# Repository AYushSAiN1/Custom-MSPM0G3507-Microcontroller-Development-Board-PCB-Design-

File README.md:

# MSPM0G3507 Microcontroller Development Board

## Overview
This project presents the design of a custom development board based on the Texas Instruments MSPM0G3507 microcontroller. The objective of this project is to explore the workflow of embedded hardware development including schematic design, PCB layout, power regulation, debugging interfaces, and communication peripherals.

The board integrates essential subsystems required for microcontroller operation such as power management, USB-UART communication, clock generation, and SWD debugging support.

---

## Key Features

- MSPM0G3507 ARM Cortex-M0+ microcontroller
- USB-C interface for power input
- 3.3V LDO voltage regulator
- USB-UART communication using CH340
- SWD debugging interface
- External crystal oscillator
- Decoupling and filtering circuitry for stable operation

---

## Hardware Architecture

### USB Interface
- USB-C connector for power input
- VBUS supply input

### Power Regulation
- 3.3V LDO voltage regulator
- Input and output filtering capacitors

### USB-UART Communication
- CH340 USB-to-UART converter
- Serial communication with MCU

### Microcontroller Core
- MSPM0G3507 MCU
- Decoupling capacitors
- GPIO expansion

### Clock Circuit
- External crystal oscillator
- Load capacitors

### Debug Interface
- ARM SWD debug header
- Reset circuitry
## Schematic Preview

---

## PCB Layout

---

## PCB 3D View

---
---
## Learning Outcomes

- Microcontroller hardware integration
- Power supply design for embedded systems
- USB-UART communication interface
- PCB schematic capture and layout
- Decoupling and grounding strategies
- SWD debugging interface design

---

## Future Improvements

- Add sensor interfaces (I2C / SPI peripherals)
- Improve PCB routing for signal integrity
- Add onboard debugging LEDs
- Integrate bootloader support

---
## Tools Used

- KiCad — schematic capture and PCB layout
- Embedded hardware design principles
- PCB routing and layout techniques

---

## License

This project is released for educational and learning purposes.

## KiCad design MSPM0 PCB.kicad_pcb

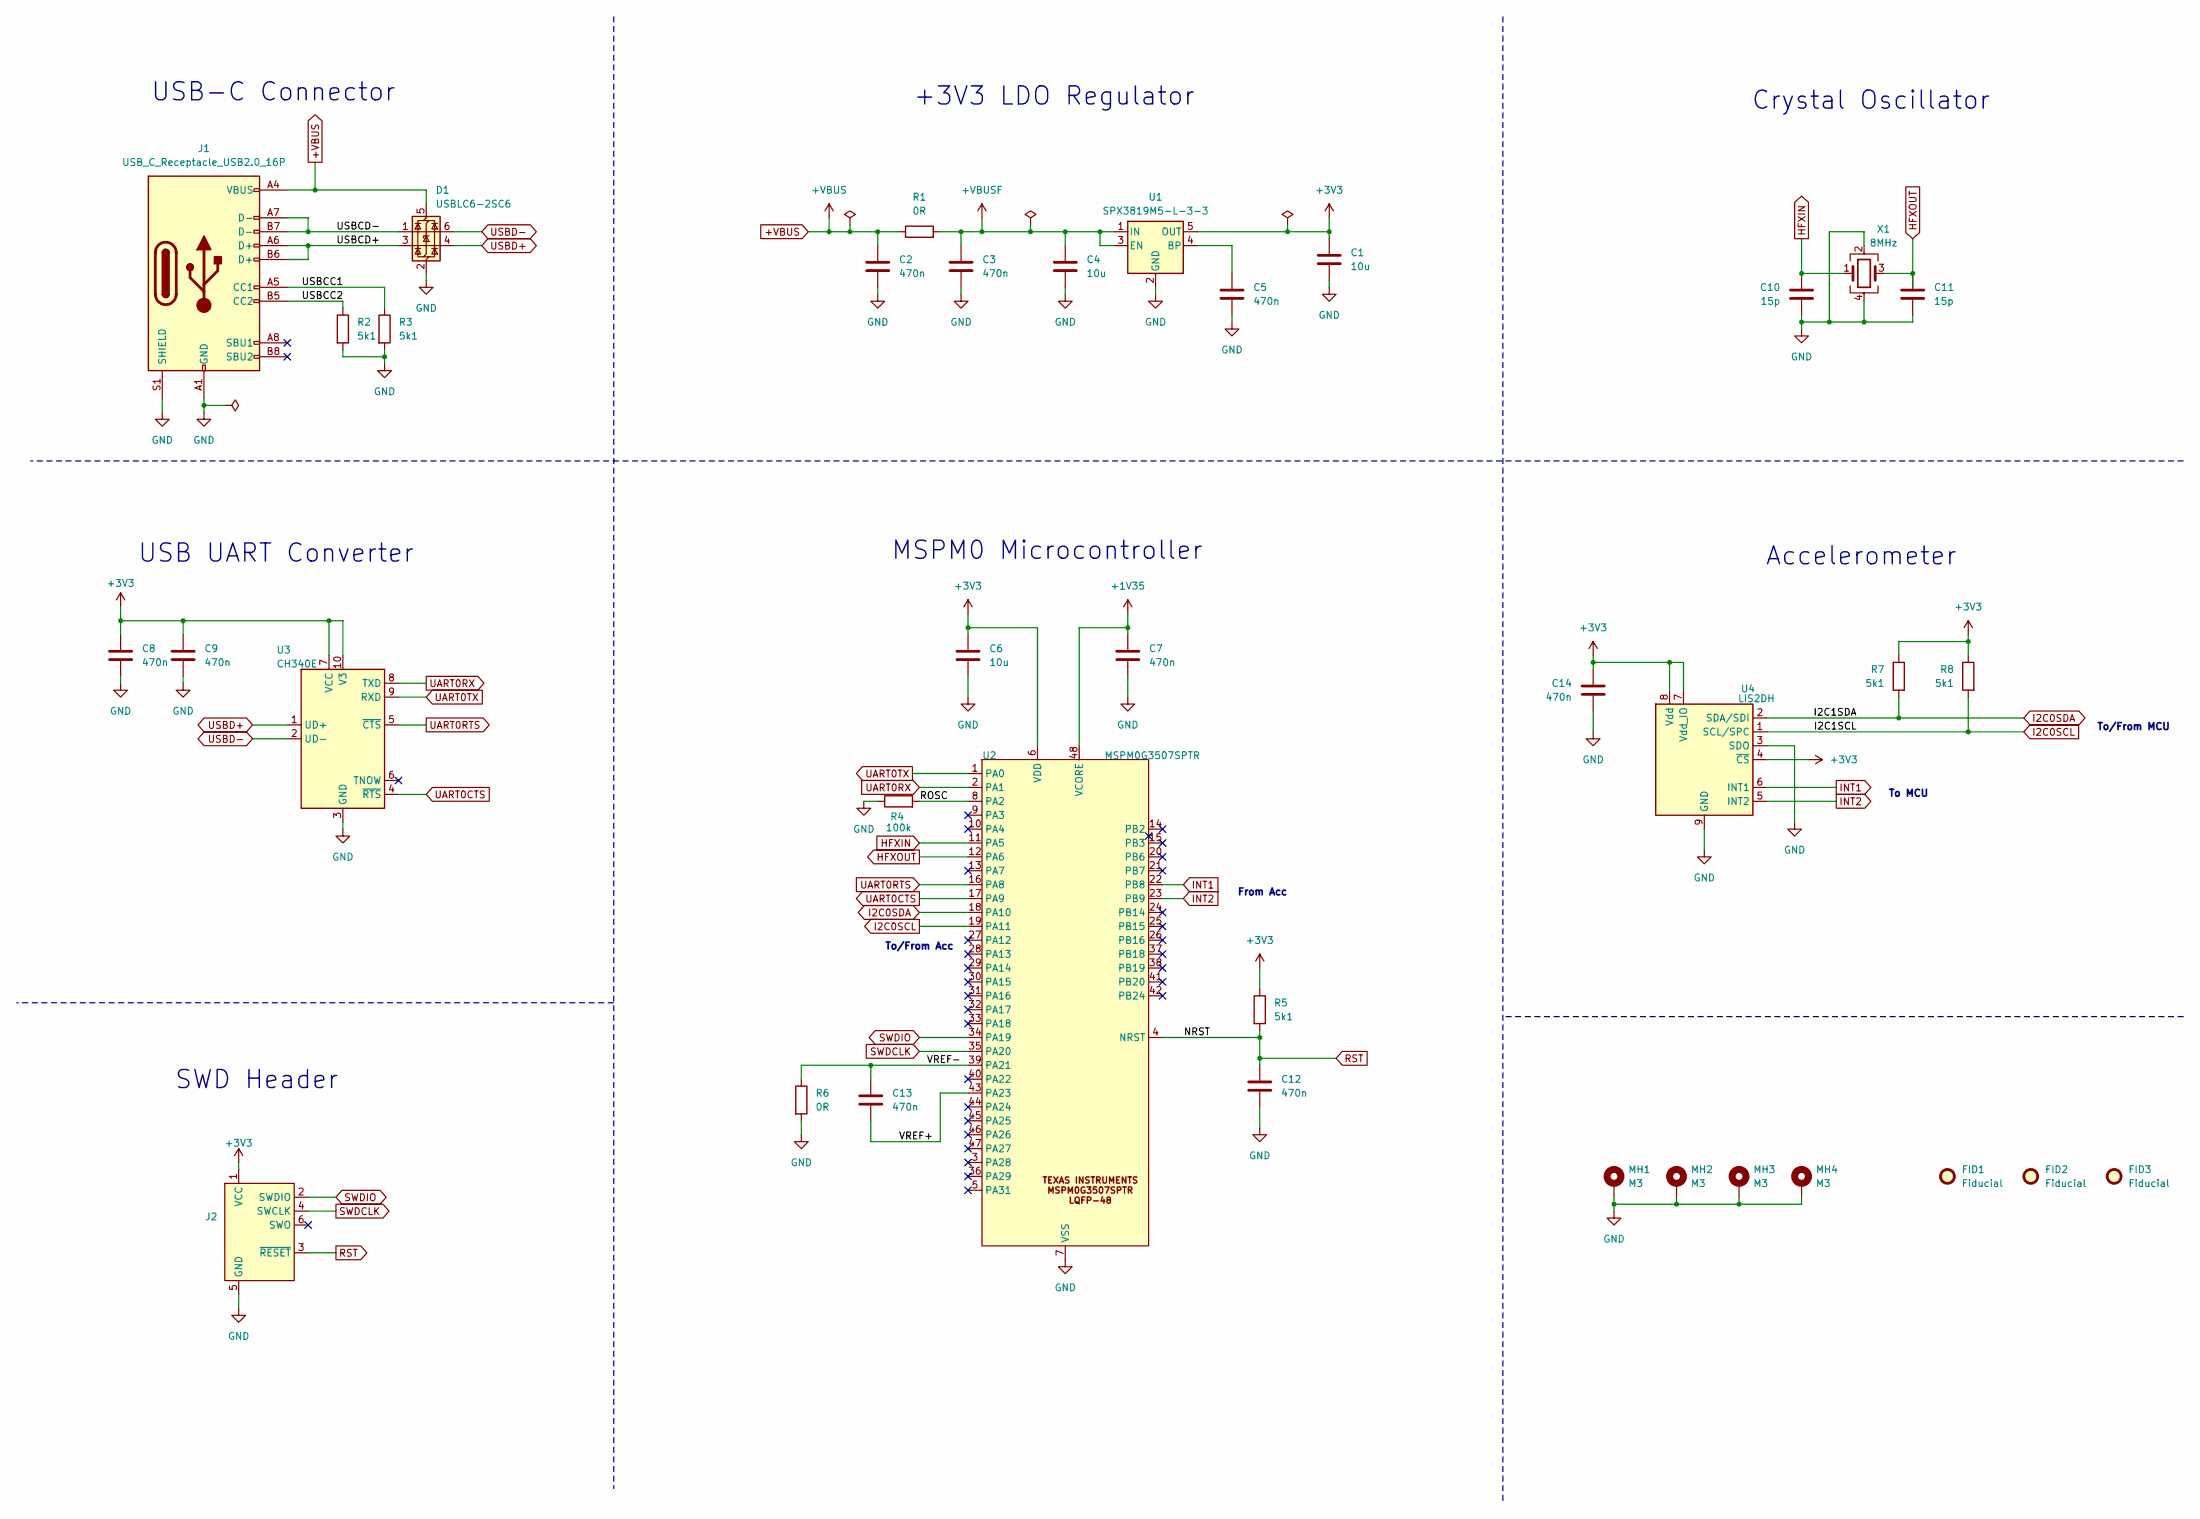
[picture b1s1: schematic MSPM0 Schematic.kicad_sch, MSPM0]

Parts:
C1, C4, C6: 10u; C_0805_2012Metric; Manufacturer Part Number CL21A106KAYNNNE; LCSC C15850
C2, C3, C5, C7, C8, C9, C12, C13, C14: 470n; C_0603_1608Metric; Manufacturer Part Number CL21B474KAFNNNE; LCSC C15972
C10, C11: 15p; C_0603_1608Metric; Manufacturer Part Number CL21B474KAFNNNE; LCSC C15972
D1: USBLC6-2SC6; SOT-23-6
FID1, FID2, FID3: Fiducial; Fiducial_1mm_Mask2mm
J1: USB_C_Receptacle_USB2.0_16P; USB_C_Receptacle_GCT_USB4105-xx-A_16P_TopMnt_Horizontal
J2: Conn_ARM_SWD_TagConnect_TC2030; Tag-Connect_TC2030-IDC-FP_2x03_P1.27mm_Vertical
MH1, MH2, MH3, MH4: M3; MountingHole_3.2mm_M3_Pad_Via
R1, R6: 0R; R_0603_1608Metric
R2, R3, R5, R7, R8: 5k1; R_0603_1608Metric
R4: 100k; R_0603_1608Metric
U1: SPX3819M5-L-3-3; SOT-23-5
U2: MSPM0G3507SPTR; LQFP-48_7x7mm_P0.5mm; Manufacturer Part Number MSPM0G3507SPTR; LCSC C22362630
U3: CH340E; MSOP-10_3x3mm_P0.5mm
U4: LIS2DH; LGA-14_2x2mm_P0.35mm_LayoutBorder3x4y
X1: 8MHz; Crystal_SMD_3225-4Pin_3.2x2.5mm; Manufacturer Part Number ASE-8.000MHZ-E-T

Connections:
+1V35: C7.1, U2.48 (VCORE)
+3V3: C1.1, C6.1, C8.1, C9.1, C14.1, J2.1 (VCC), R5.1, R7.1, R8.1, U1.5 (OUT), U2.6 (VDD), U3.7 (VCC), U3.10 (V3), U4.4 (~CS), U4.7 (Vdd_IO), U4.8 (Vdd)
+VBUS: C2.1, D1.5 (VBUS), J1.A4 (VBUS), J1.A9 (VBUS), J1.B4 (VBUS), J1.B9 (VBUS), R1.1
+VBUSF: C3.1, C4.1, R1.2, U1.1 (IN), U1.3 (EN)
/HFXIN: C10.1, U2.11 (PA5), X1.1
/HFXOUT: C11.1, U2.12 (PA6), X1.3
/NRST: C12.1, J2.3 (~RESET), R5.2, U2.4 (NRST)
/ROSC: R4.2, U2.8 (PA2)
/SWCLK: J2.4 (SWCLK), U2.35 (PA20)
/SWDIO: J2.2 (SWDIO), U2.34 (PA19)
/UART0CTS: U2.17 (PA9), U3.4 (~RTS)
/UART0RTS: U2.16 (PA8), U3.5 (~CTS)
/UART0RX: U2.2 (PA1), U3.8 (TXD)
/UART0TX: U2.1 (PA0), U3.9 (RXD)
/USBCC1: J1.A5 (CC1), R3.1
/USBCC2: J1.B5 (CC2), R2.1
/USBCD+: D1.3 (I/O2), J1.A6 (D+), J1.B6 (D+)
/USBCD-: D1.1 (I/O1), J1.A7 (D-), J1.B7 (D-)
/USBD+: D1.4 (I/O2), U3.1 (UD+)
/USBD-: D1.6 (I/O1), U3.2 (UD-)
/VREF+: C13.2, U2.43 (PA23)
/VREF-: C13.1, R6.1, U2.39 (PA21)
GND: C1.2, C2.2, C3.2, C4.2, C5.2, C6.2, C7.2, C8.2, C9.2, C10.2, C11.2, C12.2, C14.2, D1.2 (GND), J1.A1 (GND), J1.A12 (GND), J1.B1 (GND), J1.B12 (GND), J1.S1 (SHIELD), J2.5 (GND), MH1.1, MH2.1, MH3.1, MH4.1, R2.2, R3.2, R4.1, R6.2, U1.2 (GND), U2.7 (VSS), U3.3 (GND), U4.3 (SDO), U4.9 (GND), X1.2, X1.4
I2C0SCL: R8.2, U2.19 (PA11), U4.1 (SCL/SPC)
I2C0SDA: R7.2, U2.18 (PA10), U4.2 (SDA/SDI)
INT1: U2.22 (PB8), U4.6 (INT1)
INT2: U2.23 (PB9), U4.5 (INT2)
unnamed: C5.1, U1.4 (BP)
unnamed: U4.10 (GND), U4.12 (GND)

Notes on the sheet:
From Acc
SWD Header
USB UART Converter
To/From Acc
To/From MCU
+3V3 LDO Regulator
To MCU
Crystal Oscillator
MSPM0 Microcontroller
Accelerometer
USB-C Connector

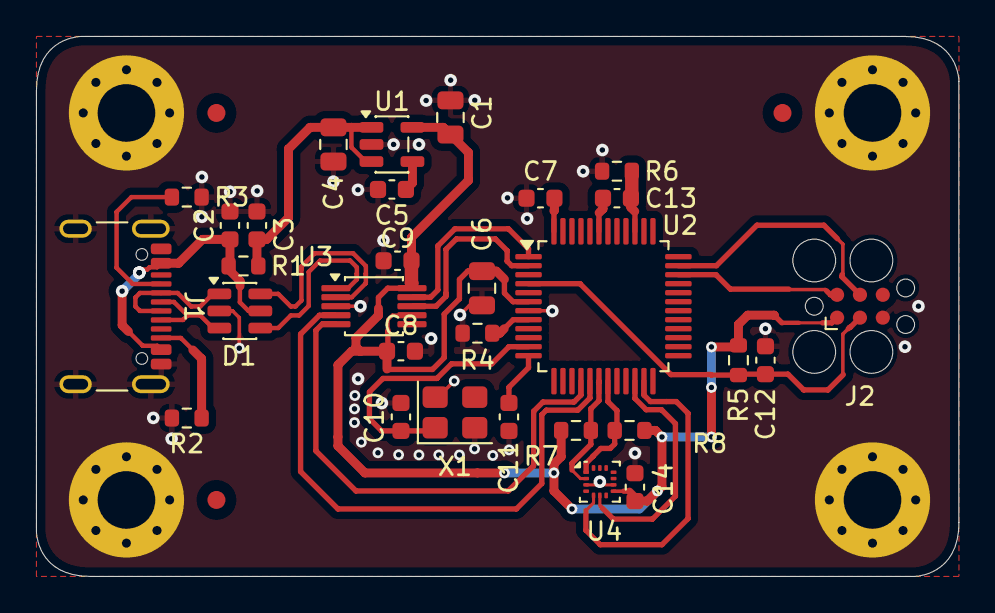
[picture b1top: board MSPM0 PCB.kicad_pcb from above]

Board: 2 copper layers, 51.2 x 30.0 mm, 37 parts (0 on the bottom side), 29 nets.

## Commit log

2026-03-05 Add README for MSPM0G3507 development board project
    This README provides an overview of the MSPM0G3507 microcontroller development board project, detailing its features, hardware architecture, learning outcomes, future improvements, tools used, and li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
